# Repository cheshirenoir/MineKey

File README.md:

# MineKey
A very silly project to build a "better" keyboard for Modded Minecraft.  

##Prerequisites:
You'll need to include the following libraries. They're availabe from the Arduino Library manager  
https://github.com/lostcaggy/rotary_caggy  
https://github.com/adafruit/Adafruit_BusIO  
https://github.com/adafruit/Adafruit-GFX-Library  
https://github.com/adafruit/Adafruit_SSD1306  
Use the Earlphilhower Raspberry Pi Pico board definition https://github.com/earlephilhower/arduino-pico  

##Installation:
Drag the UF2 file to your Pico and that should be it.  

##Compiling
You'll need to put the contents of the libraries folder in your local libraries folder. It contains a modified version of the original keyboard.h file.  

##Some thanks
Brendan and Michael for putting up with my stupid comments and fumblling.  
lostcaggy - This person deserves kudos! This is the first and only library I have found to handle rotary encoders on the Raspberry Pi Pico properly.  
Earlphilhowe - Your work allowed me to actually finish this project!  
johnwasser in the Arduino forums - Your keyboard mod worked to let me generate raw keys for all my keyboards  

##Latest HW differences
Revised schematic with better pin mappings and a spot for a 128x64 OLED rather than the 128x32 I used in the original proto board.  

##Current Key mappings:
I probably should move these to an external file that you can drag into the Pico, but I don't know how to do that. Someone else can add that functionality :-D  

No modifier implements a Numeric Keypad. Row by row, the keys are:  
> 7, 8, 9, /  
> 4, 5, 6, *  
> 1, 2, 3, -  
> 0, stop, return, +   

With the upper META key held down, you mostly get additional function keys. Row by row, the keys are:  
> F13, F14, F15, F16  
> F17, F18, F19, F20  
> F21, F22, F23, F24  
> KEY_OPEN, KEY_HELP, KEY_PROPS, KEY_FRONT  

With the lower SUPER key held down, you get multimedia keys. Row by row, the keys are:  
> KEY_MEDIA_PLAYPAUSE, KEY_MEDIA_STOPCD, KEY_MEDIA_PREVIOUSSONG, KEY_MEDIA_NEXTSONG  
> KEY_MEDIA_EJECTCD, KEY_MEDIA_WWW, KEY_MEDIA_BACK, KEY_MEDIA_FORWARD  
> KEY_MEDIA_STOP, KEY_MEDIA_FIND, KEY_MEDIA_SCROLLUP, KEY_MEDIA_SCROLLDOWN  
> KEY_MEDIA_EDIT, KEY_MEDIA_COFFEE, KEY_MEDIA_REFRESH, KEY_MEDIA_CALC  

With both SUPER and META held down gets you all sorts of random keys. Many probably won't work. Row by row, the keys are:  
> KEY_KPCOMMA, KEY_YEN, KEY_KATAKANAHIRAGANA, KEY_HENKAN  
> Keypad_A, Keypad_B, Keypad_C, Keypad_D  
> Keypad_E, Keypad_F, Keypad_00, Keypad_000  
> Keypad_XOR, Keypad_@, Keypad_+/-, Keypad_!  

CC-BY-SA

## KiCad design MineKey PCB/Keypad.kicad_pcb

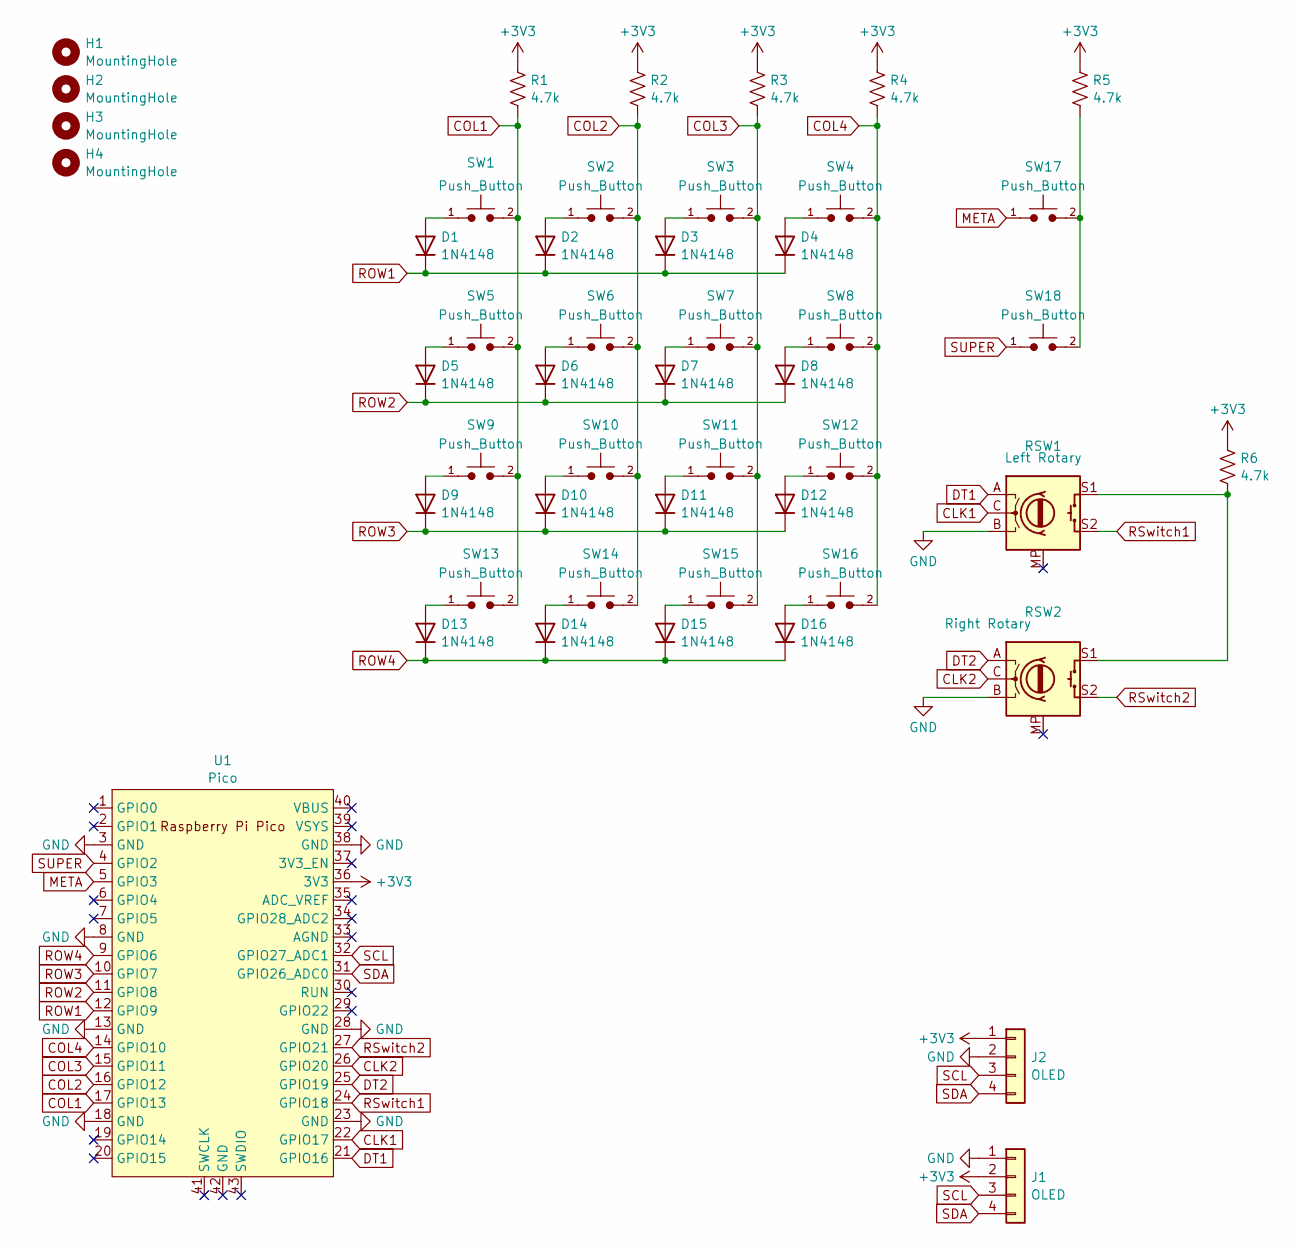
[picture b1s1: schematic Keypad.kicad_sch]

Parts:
D1, D2, D3, D4, D5, D6, D7, D8, D9, D10, D11, D12, D13, D14, D15, D16: 1N4148; D_5W_P10.16mm_Horizontal
H1, H2, H3, H4: MountingHole; MountingHole_3.2mm_M3
J1, J2: OLED; PinHeader_1x04_P2.54mm_Vertical
R1, R2, R3, R4, R5, R6: 4.7k; R_Axial_DIN0309_L9.0mm_D3.2mm_P12.70mm_Horizontal
RSW1: Left Rotary; RotaryEncoder_Alps_EC12E-Switch_Vertical_H20mm
RSW2: Right Rotary; RotaryEncoder_Alps_EC12E-Switch_Vertical_H20mm
SW1, SW2, SW3, SW4, SW5, SW6, SW7, SW8, SW9, SW10, SW11, SW12, SW13, SW14, SW15, SW16: Push_Button; SW_Cherry_MX_1.00u_PCB
SW17, SW18: Push_Button; SW_Cherry_MX_2.00u_PCB
U1: Pico; RPi_Pico_SMD_TH

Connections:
+3V3: J1.2, J2.1, R1.1, R2.1, R3.1, R4.1, R5.1, R6.1, U1.36 (3V3)
CLK1: RSW1.C, U1.22 (GPIO17)
CLK2: RSW2.C, U1.26 (GPIO20)
COL1: R1.2, SW1.2, SW5.2, SW9.2, SW13.2, U1.17 (GPIO13)
COL2: R2.2, SW2.2, SW6.2, SW10.2, SW14.2, U1.16 (GPIO12)
COL3: R3.2, SW3.2, SW7.2, SW11.2, SW15.2, U1.15 (GPIO11)
COL4: R4.2, SW4.2, SW8.2, SW12.2, SW16.2, U1.14 (GPIO10)
DT1: RSW1.A, U1.21 (GPIO16)
DT2: RSW2.A, U1.25 (GPIO19)
GND: J1.1, J2.2, RSW1.B, RSW2.B, U1.3 (GND), U1.8 (GND), U1.13 (GND), U1.18 (GND), U1.23 (GND), U1.28 (GND), U1.38 (GND)
META: SW17.1, U1.5 (GPIO3)
unnamed: D1.2 (A), SW1.1
unnamed: D2.2 (A), SW2.1
unnamed: D3.2 (A), SW3.1
unnamed: D4.2 (A), SW4.1
unnamed: D5.2 (A), SW5.1
unnamed: D6.2 (A), SW6.1
unnamed: D7.2 (A), SW7.1
unnamed: D8.2 (A), SW8.1
unnamed: D9.2 (A), SW9.1
unnamed: D10.2 (A), SW10.1
unnamed: D11.2 (A), SW11.1
unnamed: D12.2 (A), SW12.1
unnamed: D13.2 (A), SW13.1
unnamed: D14.2 (A), SW14.1
unnamed: D15.2 (A), SW15.1
unnamed: D16.2 (A), SW16.1
unnamed: R5.2, SW17.2, SW18.2
unnamed: R6.2, RSW1.S1, RSW2.S1
ROW1: D1.1 (K), D2.1 (K), D3.1 (K), D4.1 (K), U1.12 (GPIO9)
ROW2: D5.1 (K), D6.1 (K), D7.1 (K), D8.1 (K), U1.11 (GPIO8)
ROW3: D9.1 (K), D10.1 (K), D11.1 (K), D12.1 (K), U1.10 (GPIO7)
ROW4: D13.1 (K), D14.1 (K), D15.1 (K), D16.1 (K), U1.9 (GPIO6)
RSwitch1: RSW1.S2, U1.24 (GPIO18)
RSwitch2: RSW2.S2, U1.27 (GPIO21)
SCL: J1.3, J2.3, U1.32 (GPIO27_ADC1)
SDA: J1.4, J2.4, U1.31 (GPIO26_ADC0)
SUPER: SW18.1, U1.4 (GPIO2)

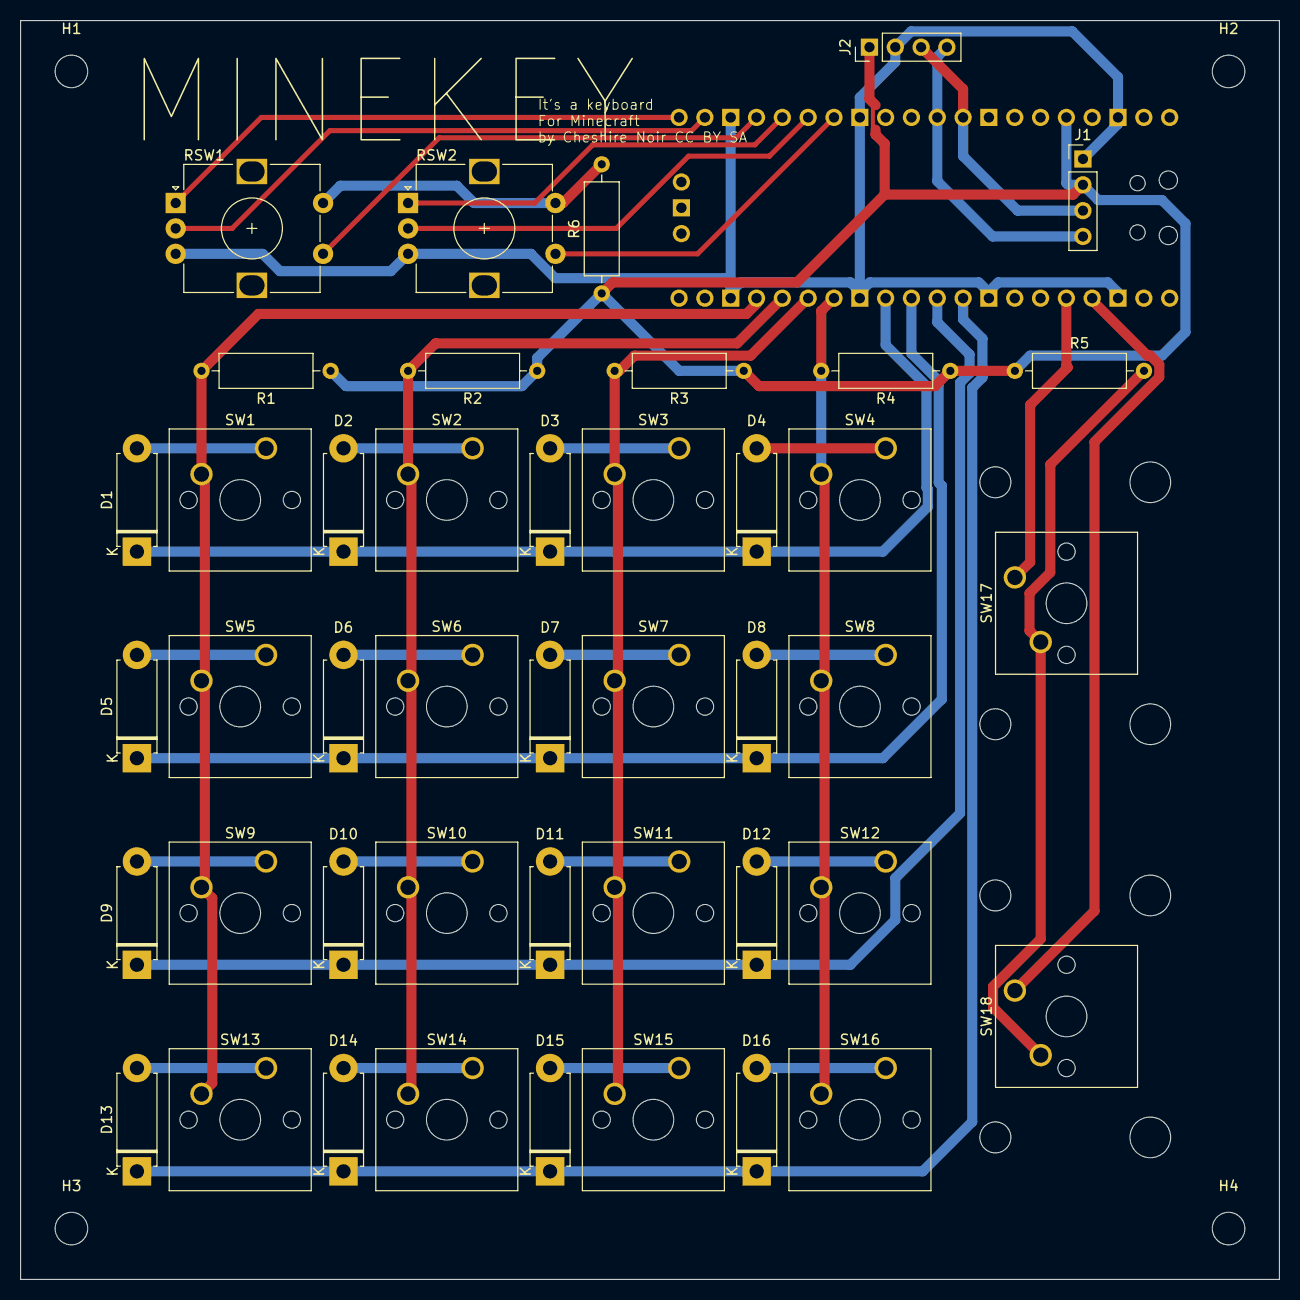
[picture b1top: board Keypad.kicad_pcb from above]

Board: 2 copper layers, 123.8 x 123.8 mm, 49 parts (1 on the bottom side), 38 nets.

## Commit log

2025-07-27 Debounced Keys all working
    After SO MANY versions, here is the first version that has actually useful functionality. It's basically a glorified numpad, but the code has now got good bones to work from.
2025-07-28 Add files via upload
    Updated with abstracted key bindings, proper support for key hold / release and META and SUPER are now bound properly
2025-08-01 Add files via upload
    HID Keys now working. They were there all along! OMG this has been a heck of a learning experience.
2025-08-17 Update README.md
    Added better library mappings and cleaned up.
    Added some thanks
2025-08-17 Add files via upload
    Modified version of Keyboard.h that supports two additional functions that allow support for raw key combos.
2025-08-17 Add files via upload
    The magically working version. Only took 17 different local releases to get her.
2025-08-17 Delete MKKeyboardWorking.ino
    Old working version. Removed for clarity
2025-08-17 Add files via upload
    UF2. Drag and drop?
2025-08-17 Update README.md
    Better formatting (I hope)

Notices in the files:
MineKey PCB/Keypad.kicad_pcb:
by Cheshire Noir CC BY SA
